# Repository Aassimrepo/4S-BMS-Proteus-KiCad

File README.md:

# 4S Battery Management System (BMS)

### Proteus Simulation & KiCad PCB Design

A simulation-based **4S Battery Management System (BMS)** designed to monitor individual battery cells, estimate pack state, detect abnormal operating conditions, and control passive cell balancing.

The project combines **Arduino-based embedded control, Proteus circuit simulation, and KiCad PCB design** to develop and validate the BMS architecture before physical hardware fabrication.

---

## Overview

A Battery Management System is responsible for monitoring and protecting rechargeable battery packs during charging and discharging.

This project implements a **4-series-cell (4S) BMS**, where each individual cell is monitored independently. The system measures cell voltage, pack voltage, current, and temperature while providing protection and balancing functionality.

The complete design was developed and tested in simulation using **Proteus**, while the corresponding PCB was designed and routed using **KiCad**.

> **Note:** This is a simulation and PCB-design project. No physical battery hardware is used in the current implementation.

---

## Key Features

* Individual voltage monitoring for all **4 battery cells**
* Total battery pack voltage calculation
* Battery **State of Charge (SOC)** estimation
* Overvoltage protection
* Undervoltage protection
* Overcurrent detection
* Overtemperature detection
* Passive cell-balancing control
* Individual cell-balancing indicators
* Charge and load status indication
* Fault indication
* ACS712-based current sensing model
* NTC thermistor temperature sensing
* Nokia 5110 LCD monitoring
* Arduino-based embedded control
* Serial telemetry between controllers
* Complete KiCad schematic and PCB layout
* PCB routing and Design Rules Check (**DRC**)

---

## System Architecture

```text
                     ┌──────────────────────┐
                     │      4S Battery      │
                     │   Cell 1 - Cell 4   │
                     └──────────┬───────────┘
                                │
                                ▼
                     ┌──────────────────────┐
                     │   Voltage Divider    │
                     │   Sensing Network    │
                     └──────────┬───────────┘
                                │
                                ▼
                 ┌──────────────────────────────┐
                 │      Arduino BMS Controller  │
                 │                              │
                 │ • Cell Voltage Monitoring    │
                 │ • Pack Voltage Calculation   │
                 │ • SOC Estimation             │
                 │ • Fault Detection            │
                 │ • Balancing Control          │
                 └───────┬──────────┬───────────┘
                         │          │
              ┌──────────┘          └───────────┐
              ▼                                 ▼
      ┌───────────────┐                 ┌───────────────┐
      │  Nokia 5110   │                 │ Status / Fault│
      │     LCD       │                 │     LEDs      │
      └───────────────┘                 └───────────────┘
                         │
                         ▼
                 ┌─────────────────┐
                 │ Secondary MCU / │
                 │ Telemetry Link  │
                 └─────────────────┘
```

---

## Cell Voltage Measurement

The four battery-cell inputs are measured using resistor-divider networks connected to the Arduino's analog inputs.

The divider networks allow the cumulative battery tap voltages to be scaled into a measurable ADC range.

| Cell   | Divider Network | Software Scaling |
| ------ | --------------- | ---------------: |
| Cell 1 | 10k / 10k       |               ×2 |
| Cell 2 | 20k / 10k       |               ×3 |
| Cell 3 | 30k / 10k       |               ×4 |
| Cell 4 | 40k / 10k       |               ×5 |

The controller converts the measured ADC values into cell-voltage estimates and calculates the pack voltage from the four cell measurements.

---

## Battery Monitoring

The system continuously monitors:

* Cell 1 voltage
* Cell 2 voltage
* Cell 3 voltage
* Cell 4 voltage
* Pack voltage
* State of Charge (SOC)
* Battery current
* Battery temperature

ADC averaging and software filtering are used to reduce measurement fluctuations and reject invalid readings during simulation.

---

## Protection System

The BMS evaluates the measured parameters against configurable safety thresholds.

### Overvoltage

Each cell voltage is independently checked against the configured overvoltage threshold.

### Undervoltage

Each cell is monitored for voltage falling below the configured undervoltage threshold.

### Overcurrent

The ACS712 sensor model provides the current measurement. The calculated current is compared with the configured current limit.

### Overtemperature

An NTC thermistor model is used to estimate battery temperature. The system generates an overtemperature condition when the configured temperature threshold is exceeded.

### Fault Indication

When a protection condition is detected, the BMS updates its fault state and controls the corresponding protection/status outputs.

---

## Passive Cell Balancing

The BMS implements simulated passive balancing for each individual cell.

```text
Cell 1 ──► BAL1
Cell 2 ──► BAL2
Cell 3 ──► BAL3
Cell 4 ──► BAL4
```

Each balancing channel can be activated independently depending on the measured cell voltage.

The balancing state is also encoded into a telemetry value for communication to the secondary controller.

---

## LCD Interface

A **Nokia 5110 LCD** provides local monitoring of the simulated battery system.

The display provides multiple monitoring pages containing:

### Cell Monitoring

* Cell 1 voltage
* Cell 2 voltage
* Cell 3 voltage
* Cell 4 voltage
* Pack voltage
* SOC

### Current & Temperature

* Battery current
* Battery temperature

### Pack Summary

* Pack voltage
* SOC
* Telemetry status

---

## Controller Communication

The primary controller periodically transmits monitoring information to the secondary controller through serial communication.

The telemetry packet contains:

```text
Cell 1
Cell 2
Cell 3
Cell 4
Pack Voltage
SOC
Current
Temperature
Fault Code
Balancing Code
```

### Fault Codes

| Code | Condition       |
| ---: | --------------- |
|    0 | No Fault        |
|    1 | Overvoltage     |
|    2 | Undervoltage    |
|    3 | Overcurrent     |
|    4 | Overtemperature |

The balancing status is represented using a bit-coded value, allowing the state of the four balancing channels to be transmitted efficiently.

---

## Proteus Simulation

The complete BMS control system is simulated in **Proteus**.

The simulation models:

* Battery-cell voltage inputs
* Voltage-divider sensing circuits
* Arduino controllers
* ACS712 current sensor
* NTC thermistor
* Nokia 5110 LCD
* Status LEDs
* Cell-balancing outputs
* Serial communication

Different operating conditions can be introduced by changing the simulated sensor and battery inputs.

This allows the BMS control logic to be evaluated without physical battery hardware.

---

## PCB Design

The corresponding BMS PCB was designed using **KiCad**.

The PCB design includes the circuitry required for:

* Battery connections
* Cell-voltage sensing
* Current sensing
* Temperature sensing
* Microcontroller interfaces
* Cell balancing
* Status indicators
* Buzzer
* Display interface
* Communication interfaces
* ESP8266 interface

The PCB was routed and subsequently checked using KiCad's Design Rules Checker.

---

## PCB Validation

The completed PCB layout was subjected to KiCad's **Design Rules Check (DRC)**.

### Final DRC Result

```text
0 Violations
```

This confirms that the final PCB layout passed the configured KiCad design-rule checks.

---

## Repository Structure

```text
4S-BMS-Proteus-KiCad/
│
├── Proteus/
│   ├── Simulation/
│   │   ├── *.dsn
│   │   └── *.pdsprj
│   │
│   ├── Arduino_Code/
│   │   ├── *.ino
│   │   └── ...
│   │
│   └── HEX_Files/
│       └── *.hex
│
├── KiCad_PCB/
│   ├── Source/
│   │   ├── *.kicad_pro
│   │   ├── *.kicad_sch
│   │   └── *.kicad_pcb
│   │
│   └── Outputs/
│       ├── PCB_3D_Render.png
│       └── PCB_Layout.png
│
├── Documentation/
│   ├── Screenshots/
│   └── Results/
│
├── .gitignore
└── README.md
```

---

## Testing

The simulated BMS can be evaluated under different operating conditions.

| Test Condition   | Input                            | Expected Behaviour             |
| ---------------- | -------------------------------- | ------------------------------ |
| Normal Operation | Normal cell voltages             | Normal monitoring              |
| Overvoltage      | Cell exceeds OV limit            | Fault/protection indication    |
| Undervoltage     | Cell falls below UV limit        | Load protection/fault          |
| Overcurrent      | Current exceeds limit            | Overcurrent protection         |
| Overtemperature  | Temperature exceeds limit        | Temperature protection         |
| Cell Balancing   | Cell reaches balancing threshold | Corresponding balancing output |
| Recovery         | Fault condition removed          | Return to normal operation     |

Screenshots demonstrating the simulation and PCB validation are available in the `Documentation/Screenshots` directory.

---

## Technologies Used

### Hardware / Controllers

* Arduino Uno
* Arduino Nano
* ESP8266 interface
* ACS712 current sensor
* NTC thermistor
* Nokia 5110 LCD
* Passive balancing circuitry

### Software

* Proteus
* KiCad
* Arduino IDE
* C/C++

---

## Future Development

The project can be extended into an IoT-enabled battery monitoring platform.

Planned extensions include:

* Raspberry Pi 5 IoT gateway
* Real-time web dashboard
* Remote BMS telemetry
* Live voltage/current/temperature graphs
* Historical data logging
* Battery-state prediction
* Machine-learning based battery analysis
* Remote fault notifications
* Physical hardware implementation and validation

These features are intended as future extensions and are **not represented as completed functionality in the current version of the repository**.

---

## Project Documentation

The repository contains screenshots showing:

* Complete Proteus simulation
* Normal BMS operation
* Fault detection
* PCB routing
* PCB 3D visualization
* KiCad DRC results

Refer to:

```text
Documentation/Screenshots/
```

for the available visual documentation.

---

## Disclaimer

This project is intended for **educational and research purposes**.

The current implementation is a simulation and PCB-design study and has not been validated on physical battery hardware.

A real battery-management system requires appropriate component selection, isolation, protection circuitry, thermal considerations, battery characterization, hardware validation, and extensive safety testing before being used with a real battery pack.

---

## Author

**Aassim Basheer**

Electronics and Communication Engineering

---

## License

This project is provided for educational and research purposes.

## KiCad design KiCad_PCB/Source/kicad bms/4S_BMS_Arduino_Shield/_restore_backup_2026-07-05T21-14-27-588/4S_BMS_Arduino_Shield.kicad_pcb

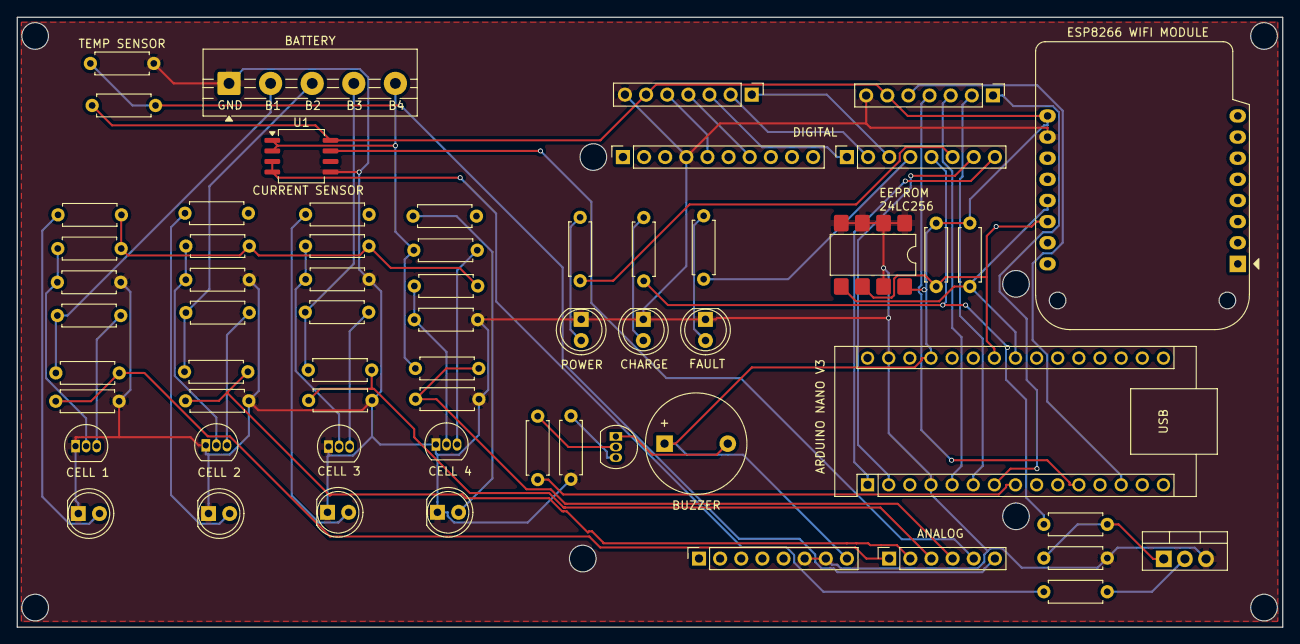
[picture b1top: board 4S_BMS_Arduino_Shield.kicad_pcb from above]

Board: 2 copper layers, 152.1 x 73.3 mm, 69 parts (0 on the bottom side), 52 nets.

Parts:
A1: ARDUINO_NANO; Arduino_Nano
BATTERY: J_BAT; TerminalBlock_MaiXu_MX126-5.0-05P_1x05_P5.00mm
BZ1: BUZZER; Buzzer_12x9.5RM7.6
D1: FAULT; LED_D5.0mm
D2: CHARGE; LED_D5.0mm
D3: POWER; LED_D5.0mm
D4: BAL_4; LED_D5.0mm
D5: BAL_3; LED_D5.0mm
D6: BAL_2; LED_D5.0mm
D7: BAL_1; LED_D5.0mm
H1, H2, H3, H4: MountingHole_Pad; MountingHole_3.2mm_M3
J1: Power; PinSocket_1x08_P2.54mm_Vertical
J2: Digital/PWM; PinSocket_1x10_P2.54mm_Vertical
J3: Analog; PinSocket_1x06_P2.54mm_Vertical
J4: Digital/PWM; PinSocket_1x08_P2.54mm_Vertical
J6: LCD_1; PinHeader_1x07_P2.54mm_Vertical
J7: LCD_2; PinHeader_1x07_P2.54mm_Vertical
MH1, MH2, MH3, MH4: MountingHole_3.2mm
Q1, Q2, Q3, Q4: 2N7000; TO-92_Inline
Q5: LOAD; TO-220-3_Vertical
Q6: BC547; TO-92_Inline
R1, R2, R4, R6, R8, R9: 10K; R_Axial_DIN0207_L6.3mm_D2.5mm_P7.62mm_Horizontal
R3: 40K; R_Axial_DIN0207_L6.3mm_D2.5mm_P7.62mm_Horizontal
R5: 30K; R_Axial_DIN0207_L6.3mm_D2.5mm_P7.62mm_Horizontal
R7: 20K; R_Axial_DIN0207_L6.3mm_D2.5mm_P7.62mm_Horizontal
R10, R11, R12, R13, R14, R16, R17, R19, R20, R21, R23, R24, R25, R27, R28: 220R; R_Axial_DIN0207_L6.3mm_D2.5mm_P7.62mm_Horizontal
R15, R18, R22, R26, R30: 100K; R_Axial_DIN0207_L6.3mm_D2.5mm_P7.62mm_Horizontal
R29, R31: 100R; R_Axial_DIN0207_L6.3mm_D2.5mm_P7.62mm_Horizontal
R32, R35: R; R_Axial_DIN0207_L6.3mm_D2.5mm_P7.62mm_Horizontal
R33, R34: 4.7K; R_Axial_DIN0207_L6.3mm_D2.5mm_P7.62mm_Horizontal
TEMP SENSOR: Thermistor_NTC; R_Axial_DIN0207_L6.3mm_D2.5mm_P7.62mm_Horizontal
U1: ACS712xLCTR-20A; SOIC-8_5.3x6.2mm_P1.27mm
U2: EEPROM; SMDIP-8_W7.62mm
U3: ESP8266; WEMOS_C3_mini

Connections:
5V: A1.27 (+5V), BZ1.1 (+), J1.8, J6.6, J7.6, R9.1, R33.1, R34.1, U1.8 (VCC), U2.8 (VCC), U3.9 (5V)
/2: J4.6, R12.2
/4: J4.4, R10.2
/7: J4.1, J6.3
/13: J2.5, J6.5
/*3: J4.5, R11.2, R29.1
/*5: J4.3, J6.1
/*6: J4.2, J6.2
/*11: J2.7, J6.4
/A0_DIV: J3.1, R1.2, R2.1
/A1_DIV: J3.2, R7.2, R8.1
/A2_DIV: J3.3, R5.2, R6.1
/A3_DIV: J3.4, R3.2, R4.1
/B1: BATTERY.2, R1.1, R27.1
/B2: BATTERY.3, R7.1, R23.1
/B3: BATTERY.4, R5.1, R19.1
/B4: BATTERY.5, R3.1, R13.1, U1.1 (IP+), U1.2 (IP+)
/BAL1: R14.2, R17.2, R21.2, R25.2, R28.2
/BUZZER: A1.8 (D5), R32.2
/CEN: A1.6 (D3), J7.2
/CLKN: A1.13 (D10), J7.5
/CURRENT_OUT: J3.5, U1.7 (VIOUT)
/DCN: A1.5 (D2), J7.3
/DINN: A1.11 (D8), J7.4
/LOAD_POS: R31.1, U1.3 (IP-), U1.4 (IP-)
/RSTN: A1.7 (D4), J7.1
/RX/0: A1.1 (D1/TX), J4.8
/SCL: A1.24 (A5), R34.2, U2.6 (SCL), U3.14 (SCL/D1)
/SDA: A1.23 (A4), R33.2, U2.5 (SDA), U3.13 (SDA/D2)
/TEMP: J3.6, R9.2, TEMP SENSOR.1
/TX/1: A1.2 (D0/RX), J4.7
GND: A1.4 (GND), A1.29 (GND), BATTERY.1, D1.1 (K), D2.1 (K), D3.1 (K), D4.1 (K), D5.1 (K), D6.1 (K), D7.1 (K), J1.6, J1.7, J2.4, J6.7, J7.7, Q1.1 (S), Q2.1 (S), Q3.1 (S), Q4.1 (S), Q5.3 (S), R2.2, R4.2, R6.2, R8.2, R15.2, R18.2, R22.2, R26.2, R30.2, R35.2, TEMP SENSOR.2, U1.5 (GND), U2.1 (A0), U2.2 (A1), U2.3 (A2), U2.4 (GND), U2.7 (WP), U3.10 (GND)
unnamed: BZ1.2 (-), Q6.1 (C)
unnamed: D1.2 (A), R10.1
unnamed: D2.2 (A), R11.1
unnamed: D3.2 (A), R12.1
unnamed: D4.2 (A), R16.1
unnamed: D5.2 (A), R20.1
unnamed: D6.2 (A), R24.1
unnamed: D7.2 (A), R28.1
unnamed: Q1.3 (D), R13.2
unnamed: Q1.2 (G), R14.1, R15.1
unnamed: Q2.3 (D), R19.2
unnamed: Q2.2 (G), R17.1, R18.1
unnamed: Q3.3 (D), R23.2
unnamed: Q3.2 (G), R21.1, R22.1
unnamed: Q4.3 (D), R27.2
unnamed: Q4.2 (G), R25.1, R26.1
unnamed: Q5.2 (D), R31.2
unnamed: Q5.1 (G), R29.2, R30.1
unnamed: Q6.2 (B), R32.1
unnamed: Q6.3 (E), R35.1
